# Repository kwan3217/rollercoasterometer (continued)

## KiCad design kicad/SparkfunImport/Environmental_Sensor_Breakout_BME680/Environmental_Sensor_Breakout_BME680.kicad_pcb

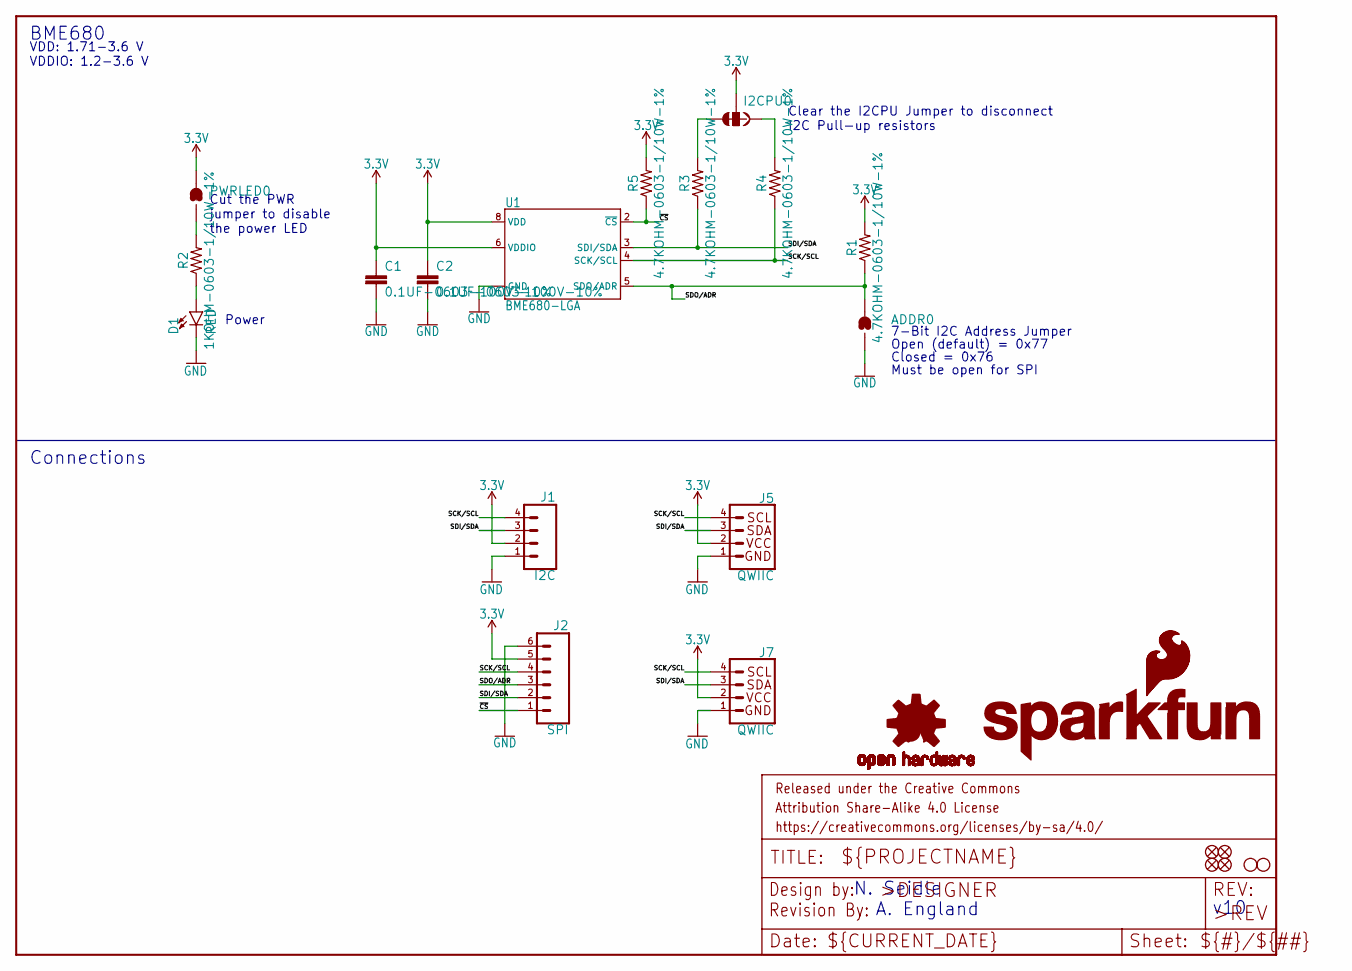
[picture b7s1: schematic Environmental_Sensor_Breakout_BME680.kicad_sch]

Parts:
ADDR0: JUMPER-SMT_2_NO_SILK; SMT-JUMPER_2_NO_SILK
C1, C2: 0.1UF-0603-100V-10%; C_0603_1608Metric
D1: RED; LED-0603
FD1, FD2, FD3, FD4: FIDUCIALUFIDUCIAL; FIDUCIAL-MICRO
FRAME1: FRAME-LETTER; CREATIVE_COMMONS
H1, H2: STAND-OFFTIGHT; STAND-OFF-TIGHT
I2CPU0: JUMPER-SMT_3_2-NC_TRACE_SILK; SMT-JUMPER_3_2-NC_TRACE_SILK
J1: I2C; 1X04_NO_SILK
J2: SPI; 1X06_NO_SILK
J5, J7: QWIIC; JST_SH_SM04B-SRSS-TB_1x04-1MP_P1.00mm_Horizontal
LOGO1: OSHW-LOGOMINI; OSHW-LOGO-MINI
LOGO2: SFE_LOGO_NAME_FLAME.1_INCH; SFE_LOGO_NAME_FLAME_.1
LOGO3: REVISION
LOGO4: SFE_LOGO_FLAME.1_INCH; SFE_LOGO_FLAME_.1
PWRLED0: JUMPER-SMT_2_NC_TRACE_SILK; SMT-JUMPER_2_NC_TRACE_SILK
R1, R3, R4, R5: 4.7KOHM-0603-1/10W-1%; R_0603_1608Metric
R2: 1KOHM-0603-1/10W-1%; R_0603_1608Metric
U1: BME680-LGA; Bosch_LGA-8_3x3mm_P0.8mm_ClockwisePinNumbering

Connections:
3.3V: C1.1, C2.1, I2CPU0.2, J1.2, J2.5, J5.2, J7.2, PWRLED0.2, R1.2, R5.2, U1.6 (VDDIO), U1.8 (VDD)
/SCK/SCL: J1.4, J2.4, J5.4, J7.4, R4.1, U1.4 (SCK/SCL)
/SDI/SDA: J1.3, J2.2, J5.3, J7.3, R3.1, U1.3 (SDI/SDA)
/SDO/ADR: ADDR0.2, J2.3, R1.1, U1.5 (SDO/ADR)
/~CS: J2.1, R5.1, U1.2 (~CS)
GND: ADDR0.1, C1.2, C2.2, D1.C, J1.1, J2.6, J5.1, J7.1, U1.1 (GND), U1.7 (GND)
unnamed: D1.A, R2.1
unnamed: I2CPU0.1, R4.2
unnamed: I2CPU0.3, R3.2
unnamed: PWRLED0.1, R2.2

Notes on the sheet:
7-Bit I2C Address Jumper
Connections
Clear the I2CPU Jumper to disconnect I2C Pull-up resistors
BME680
VDD: 1.71-3.6 V VDDIO: 1.2-3.6 V
Cut the PWR jumper to disable the power LED
Closed = 0x76
Power
N. Seidle
A. England
Open (default) = 0x77
Must be open for SPI
v10

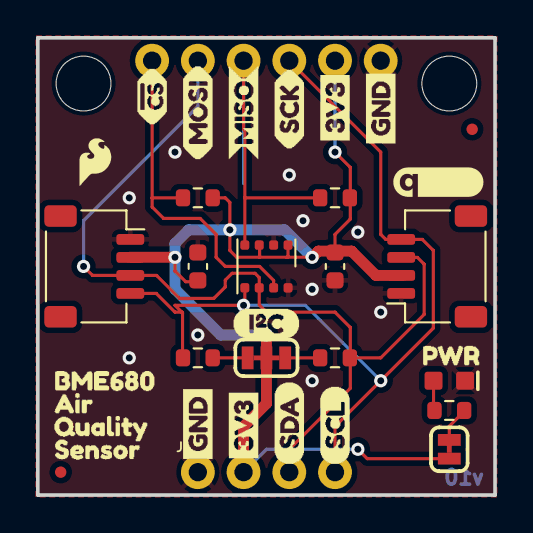
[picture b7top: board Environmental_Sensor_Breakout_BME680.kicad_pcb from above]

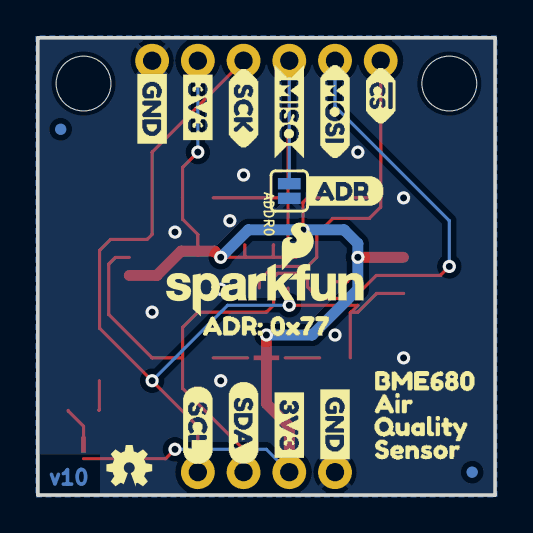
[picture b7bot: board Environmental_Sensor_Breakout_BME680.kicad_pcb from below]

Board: 2 copper layers, 25.4 x 25.4 mm, 60 parts (21 on the bottom side), 10 nets.

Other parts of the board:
U$1, U$2: MISO_O
U$3, U$4: !CS_I
U$5, U$6: MOSI_I
U$7, U$8: SCK_I
U$9, U$10, U$16, U$17: 3V3_P
U$11, U$12, U$13, U$14: GND_P
U$15: I2C
U$18, U$19: SDA_IO
U$20, U$21: SCL_IO
U$22, U$26: BME6800
U$23, U$27: AIR1
U$24, U$28: QUALITY2
U$25, U$29: SENSOR3
U$30: ADR4
U$32: QWIIC_5MM
U$33: ADR#_0X770
U$34: PWR_TO

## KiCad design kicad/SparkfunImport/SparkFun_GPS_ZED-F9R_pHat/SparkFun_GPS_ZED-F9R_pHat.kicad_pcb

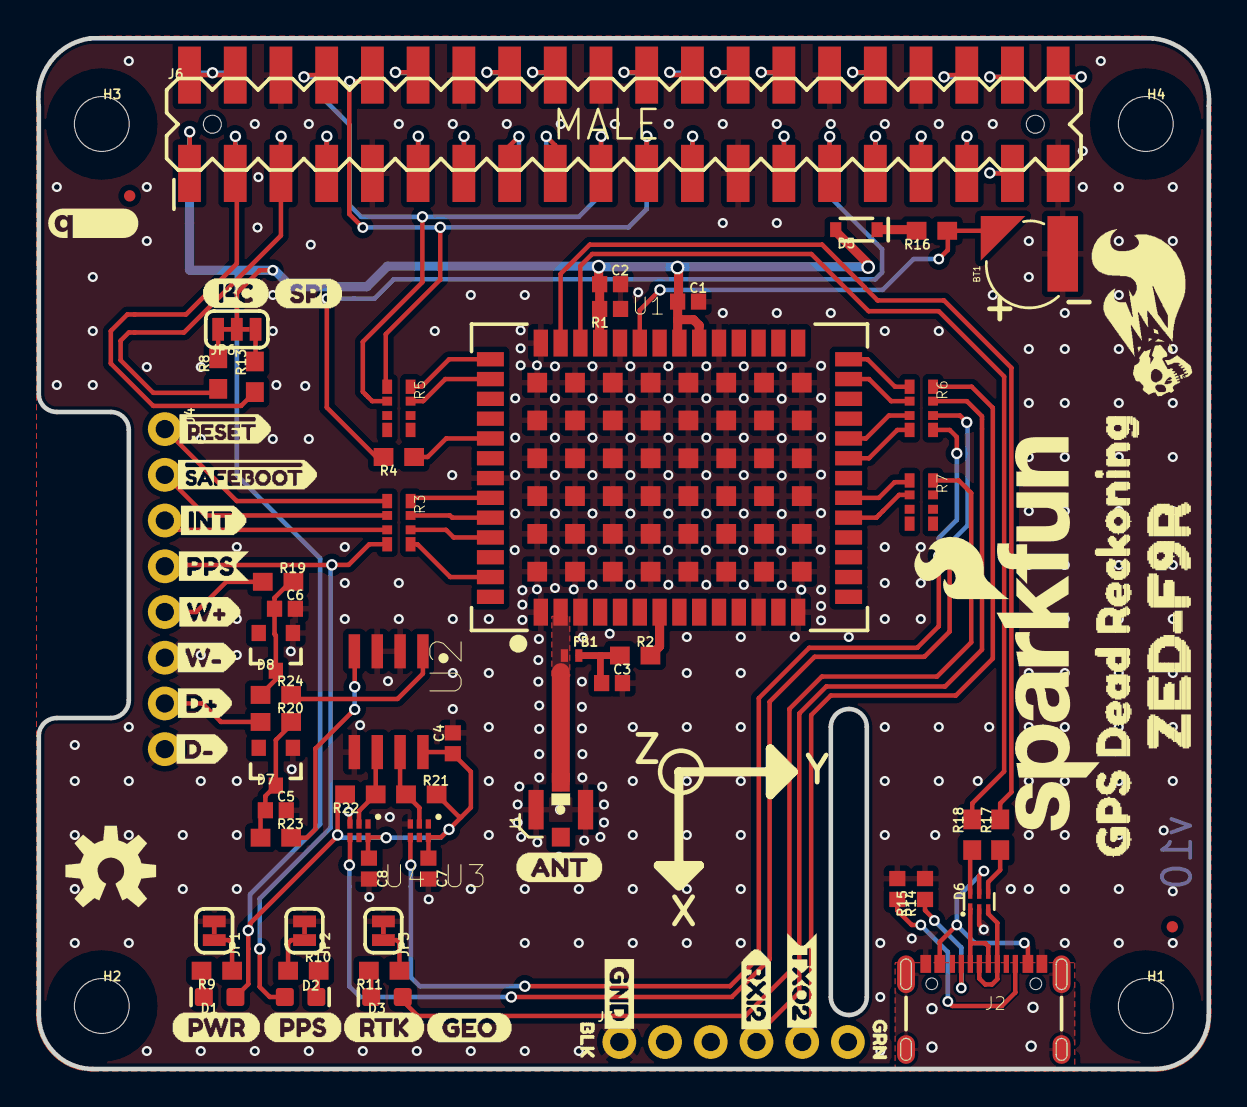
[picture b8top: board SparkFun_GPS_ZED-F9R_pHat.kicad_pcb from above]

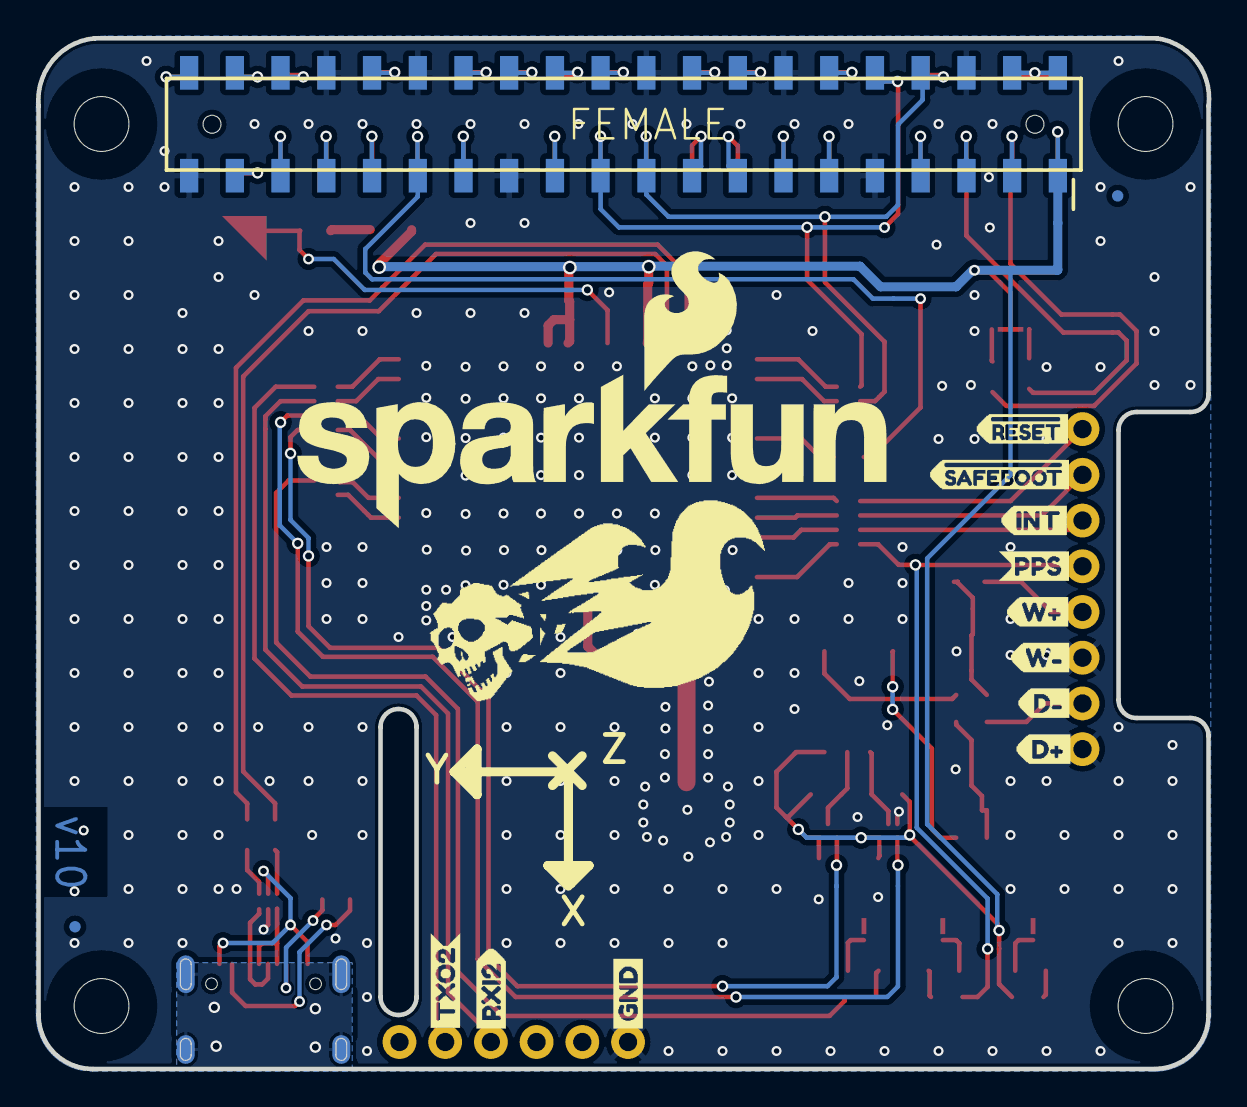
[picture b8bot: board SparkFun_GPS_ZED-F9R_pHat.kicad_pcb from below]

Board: 2 copper layers, 65.0 x 57.3 mm, 101 parts (15 on the bottom side), 84 nets.

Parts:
BT1: ML414H_IV01E_BATTERY; ML414H_IV01E
C1, C2: 1.0uF; 0402
C3: 47pF; 0402
C4, C7, C8: 0.1uF; 0402
C5, C6: 1nF; 0402
D1: RED; LED-0603
D2, D3: BLUE; LED-0603
D5: 0.5A/40V/420mV; SOD-323
D6: PRTR5V0U2F; SOT886
D7, D8: 15V; SOT23-3
FB1: 120NH; 0402_MURATA
FD1, FD2, FD3, FD4: FIDUCIALUFIDUCIAL; FIDUCIAL-MICRO
FRAME1: FRAME-LEDGER; CREATIVE_COMMONS
H1, H2, H3, H4: STAND-OFFTIGHT; STAND-OFF-TIGHT
J1: U.FL
J2: USB-C-16P
J3: 1X06_NO_SILK
J4: 1X08_NO_SILK
J6: RASPBERRYPI-40-PIN-GPIO_SMD_STACK_NOHOLES_NOREF; RASPBERRY_PI_HAT_40_PIN_SMD_STACKABLE_NOHOLES_NOREF
JP1, JP2, JP3: JUMPER-SMT_2_NC_TRACE_SILK; SMT-JUMPER_2_NC_TRACE_SILK
JP6: JUMPER-SMT_3_2-NC_TRACE_SILK; SMT-JUMPER_3_2-NC_TRACE_SILK
LOGO1: QWIIC_LOGO_5MM; QWIIC_5MM
LOGO2: OSHW-LOGOM; OSHW-LOGO-M
LOGO3: SFE_LOGO_NAME_FLAME.2_INCH; SFE_LOGO_NAME_FLAME_.2
R1: 100K; 0402
R2, R4: 33; 0603
R3, R5, R6, R7: 33; 1206_RA
R8, R13: 2.2k; 0603
R9, R10, R11: 1k; 0603
R14, R15: 5.1k; 0402
R16, R19, R20: 3.3k; 0603
R17, R18: 27; 0603
R21, R22: 910; 0603
R23, R24: 470; 0603
U1: U-BLOX_ZED_F9R; UBLOX_ZED_F9R
U2: DUAL-OPTO_HCPL-073L; SOP_8-PIN
U3, U4: UHS_INVERTER_SCHMITT_TRIGGERSIP6; SIP6
U$1: INT1
U$2: PPS4
U$3: PPS6
U$4: PWR7
U$5: RTK5
U$6: RXI28
U$7: #RESET1
U$8: #RESET2
U$9: SFE_LOGO_NAME_FLAME_.3
U$10: TXO21
U$11: INT2
U$12: PPS1
U$13: #SAFEBOOT0
U$14: RXI26
U$15: #SAFEBOOT3
U$16: TXO25
U$17: BLK2
U$18, U$19: GND-04
U$20: I_SUPER2_C-()-04
U$21: ANT1
U$22, U$32: D#0
U$23, U$33: D#1
U$24: SPI0
U$25: GPS_DEAD_RECKONING0
U$26: ZED#F9R0
U$27, U$34: W#2
U$28, U$35: W#3
U$29: GEO0
U$30: GRN1
U$31, U$36: DEAD#RECKONING#GPS#BOARD#SILK#FINAL#JPG

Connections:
3.3V: C1.1, C2.1, C4.1, C7.1, C8.1, D1.A, D5.A, J6.1, J6.1B, J6.17, J6.17B, JP6.2, R1.2, R21.2, R22.2, U1.P33, U1.P34, U1.P38, U2.P8, U3.P6, U4.P6
5V: J6.2, J6.2B, J6.4, J6.4B
CE1: J6.26, J6.26B
DIR+: J4.7, R20.1
DIR_IN: R23.2, U2.P4
DIR_OUT: R6.P6, U4.P4
DIR_SCHMITT: R22.1, U2.P6, U4.P2
DMINUS: R18.2, U1.P39
DPLUS: R17.2, U1.P40
GND: BT1.-, C1.2, C2.2, C3.2, C4.2, C5.2, C6.2, C7.2, C8.2, D6.2, D7.1, D8.1, J1.1, J1.2, J2.GND, J2.GND2, J3.1, J4.6, J4.8, J6.6, J6.6B, J6.9, J6.9B, J6.14, J6.14B, J6.20, J6.20B, J6.25, J6.25B, J6.30, J6.30B, J6.34, J6.34B, J6.39, J6.39B, JP1.1, JP2.1, JP3.1, R1.1, R14.1, R15.1, U1.G1, U1.G2, U1.G3, U1.G4, U1.G5, U1.G6, U1.G7, U1.G8, U1.G9, U1.G10, U1.G11, U1.G12, U1.G13, U1.G14, U1.G15, U1.G16, U1.G17, U1.G18, U1.G19, U1.G20, U1.G21, U1.G22, U1.G23, U1.G24, U1.G25, U1.G26, U1.G27, U1.G28, U1.G29, U1.G30, U1.G31, U1.G32, U1.G33, U1.G34, U1.G35, U1.G36, U1.G37, U1.G38, U1.G39, U1.G40, U1.G41, U1.G42, U1.G43, U1.G44, U1.G45, U1.G46, U1.G47, U1.G48, U1.P1, U1.P3, U1.P12, U1.P14, U1.P32, U1.P37, U1.P41, U1.P48, U2.P2, U2.P3, U2.P5, U3.P3, U4.P3
GP4: J6.7, J6.7B
GP6: J6.31, J6.31B
GP12: J6.32, J6.32B
GP13: J6.33, J6.33B
GP16: J6.36, J6.36B
GP17: J6.11, J6.11B
GP18: J6.12, J6.12B
GP19: J6.35, J6.35B
GP20: J6.38, J6.38B
GP21: J6.40, J6.40B
GP22: J6.15, J6.15B
GP23: J6.16, J6.16B
GP24: J6.18, J6.18B
GP25: J6.22, J6.22B
GP26: J6.37, J6.37B
GP27: J6.13, J6.13B
ID_SC: J6.28, J6.28B
ID_SD: J6.27, J6.27B
INT: J4.3, R3.P3
unnamed: JP6.1, R13.2
unnamed: D5.C, R16.2
unnamed: JP6.3, R8.2
unnamed: D1.C, R9.2
unnamed: C3.1, FB1.P2, R2.1
unnamed: D6.6, R18.1
unnamed: D6.4, R17.1
unnamed: JP1.2, R9.1
unnamed: D6.3, J2.A6, J2.B6
unnamed: D6.5, J2.VBUS1, J2.VBUS2
unnamed: D6.1, J2.A7, J2.B7
unnamed: J2.B5, R14.2
unnamed: R3.P8, U1.P49
unnamed: R3.P6, U1.P51
unnamed: R5.P6, U1.P44
unnamed: J2.A5, R15.2
unnamed: R5.P5, U1.P45
unnamed: R4.1, U1.P46
unnamed: R5.P8, U1.P42
unnamed: JP3.2, R11.1
unnamed: JP2.2, R10.1
unnamed: D2.C, R10.2
unnamed: D3.C, R11.2
unnamed: R5.P7, U1.P43
unnamed: C6.1, D8.3, R19.2, R24.1
unnamed: R7.P2, U1.P19
unnamed: R7.P1, U1.P20
unnamed: R3.P5, U1.P53
unnamed: R3.P7, U1.P50
unnamed: R6.P1, U1.P27
unnamed: R6.P2, U1.P26
unnamed: R6.P4, U1.P22
unnamed: R6.P3, U1.P23
unnamed: C5.1, D7.3, R20.2, R23.1
PPS: D2.A, J4.4, R3.P4
QWIIC_SCL: J6.5, J6.5B, R8.1
QWIIC_SDA: J6.3, J6.3B, R13.1
RF_IN: FB1.P1, J1.FEED, U1.P2
RTK_STAT: D3.A, R7.P8
RXI2: J3.4, R6.P7
RXI/MOSI: J6.8, J6.8B, J6.19, J6.19B, R5.P2
SCL/CLK: J6.23, J6.23B, R5.P4
SDA/~CS: J6.24, J6.24B, R5.P3
SHIELD: J2.SHLD1, J2.SHLD2, J2.SHLD3, J2.SHLD4, J2.SHLD5, J2.SHLD6, J2.SHLD7, J2.SHLD8
TXO2: J3.5, R6.P8
TXO/MISO: J6.10, J6.10B, J6.21, J6.21B, R5.P1
TX_READY: J6.29, J6.29B, R4.2
V_BATT: BT1.+, R16.1, U1.P36
V_RF: R2.2, U1.P7
WT+: J4.5, R19.1
WT_IN: R24.2, U2.P1
WT_OUT: R6.P5, U3.P4
WT_SCHMITT: R21.1, U2.P7, U3.P2
~RESET: J4.1, R3.P1
~SAFEBOOT: J4.2, R3.P2

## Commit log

2022-04-15 Added schematic blocks
2022-04-15 Moved stuff into a kicad folder
2022-04-15 More project checkin and reorganization
2022-04-15 Added read_sensors Arduino sketch and ICM42688 breakout
2022-04-15 Adding teensy_loader_cli as a submodule
2022-04-15 Added readme
2022-04-15 Broke down sensor block into a tree of sheets
2022-04-15 Updating README to include efforts to bring up CLI
2022-04-15 Giving up on CLI for now
2022-04-15 Adding rollercoasterometer.ino . It's not much now, but it will grow into the foundation of the program that will run on the final rollercoasterometer.
2022-04-15 Moved the Arduino sketch to its own folder, to satisfy the IDE
2022-04-18 One shining moment -- I2C_sensor lower-level stuff is working. Moving to different computer.
2022-04-18 Added Makefile and linker script for if/when we ever get back to command-line compiling
2022-04-18 Added USB+ breakout.
2022-04-18 Added a readme for the USB+ breakout
2022-04-18 Added kwan_kicad_lib as a submodule
2022-04-18 Updated README.md
    This readme is pretty much a journal of my development of the firmware for the Teensy 4.1 that will be riding on the rollercoasterometer.
2022-04-19 Moved submodule to within kicad folder
2022-04-19 Updated submodules
2022-04-19 Use updated kwan_kicad_lib
2022-04-19 Added Digikey references
2022-04-19 One shining moment
    Commit board while it still works
2022-04-20 Added AVR sketches for reading out sensors
2022-04-20 Updated symbol
    This incorporates the change in the library, to offset the NC pins and satisfy the ERC
2022-04-20 Added Digikey numbers and purposes to several parts
2022-04-20 Changed value of R436
    This is the current limiter for the battery charging. It slows down the charging, in exchange for reducing the number of different components
2022-04-20 Updated Digikey part numbers
    Darn supply chain crisis :(
2022-04-20 Updated values for I2C pullup resistors
    This weakens the pullup a little bit in exchange for a reduced part count
2022-04-20 Updated part numbers
    This sheet is included multiple times, and this time it decided to save with the references from a different instance.
2022-04-20 Added project tables
    It looks like these are appropriate to commit
2022-04-20 Updated submodule
2022-04-20 Updated part number
    Darn supply chain crisis :(
2022-04-20 Updated .gitignore to ignore bills of materials and project archives
2022-04-20 Updating PCB to follow schematic
2022-04-20 Updated graphical symbols
2022-04-20 Updated Digikey part numbers
2022-04-20 Changed resistor values to reduce component type count
2022-04-20 Changed regulator manufacturer
    New parts with identical pinout
2022-04-20 Updated graphical elements
2022-04-20 Changed protection diode for USB lines
2022-04-20 Updated Digikey part number
2022-04-20 Edited symbol to remove ERC violations
    Some of the overlapping NC pins were getting connected through the NC symbol (not connected to anything else, but connected to each other). This is fixed by editing this instance of the symbol and of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
2022-04-20 Renamed image
2022-04-20 Updated PCB
    Updated ESD diode and routing of lines through it. Added corner silkscreen marks around all LGA/BGA parts, to allow easier inspection of placement before reflow.
2022-04-20 Updated which lines are used in 4-line protection diode
2022-04-24 Added a purpose field to bypass capacitors
2022-04-24 Updated purposes for regulators
2022-04-25 Updated antenna chain
    Added a BOM-only part to give the actual antenna a Digikey reference that won't appear on the PCB. Added a solder jumper to control whether the antenna is powered. Removed 27R resistors for pins that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
2022-04-25 Updated Digikey numbers
2022-04-25 Corrected Digikey numbers
    Stupid supply chain :( . Updated protection diode for data lines. Removed heirarchical pins which are no longer present in the nested sheet.
2022-04-25 Updated kwan_kicad_lib
2022-04-25 Added joystick board
2022-04-25 Updated PCB to follow schematic changes
2022-04-25 Added reference to USB cable on BOM
2022-04-25 Updated LEDs and edge cutouts
2022-04-25 Added reference to TeensyView
    TeensyView does not get a footprint because it mounts on top of the Teensy, but it is hooked up to the schematic properly.
2022-04-25 Updated project file
2022-04-25 Replaced JS5208 with smaller JS1400
2022-04-25 Added joystick as a STEP part and used it as part of Teensy 3D model
    The whole board was saved as joystick.kicad_pcb. The parts of the board that are not part of the joystick board were removed. The board was then washed through the Freecad plugin KicadStepUp to conve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
2022-04-28 Added graphical components to schematic for joystick board
2022-04-28 Numbering change
2022-04-28 Added pocket case design files
2022-04-28 Added freecad stuff to gitignore
2022-04-28 Moved USB+ connectors to bottom of board
2022-04-28 Added #include guard
2022-04-28 Added code for ICM2 and ICM4 at the same time
2022-04-28 Added code for icm42688
2022-04-28 Added lib table stuff
2022-04-28 Updated gitignore
2022-04-29 Added a NC to the board
2022-04-29 Added code to handle SD card and write ublox packets
2022-05-14 Import from arduino-1.8.19/hardware/teensy/avr/cores/teensy4
2022-12-18 Checkin before branch
2022-12-18 Added rollercoasterometer_hat before branch
2022-12-18 Track current version of submodule
2023-03-10 Commit as-ordered shipometer 23.03
2023-03-14 Updated to KiCad 7.0
2023-03-18 Improved grounding and bypass caps on GPS
2023-03-19 Added imported Sparkfun projects. Some of them have had their footprints changed so that the 3d models work.
2023-03-19 Starting to make gps_breakout
2023-03-19 Added .gitingonre
2023-03-21 Added BME280 and ICM20948 stamps
2023-03-21 Updated several parts to kicad7, added models
2023-03-21 Added compressed wrl file
2023-03-21 Renamed
2023-03-21 Rotate IMU stamp to match GPS
2023-03-22 Update __init__.py
    check in new version of scaling script
2023-03-22 Finished and decorated IMU stamp
2023-03-24 Added labels to BME280 stamp
2023-03-24 Added labels to white LEDs
2023-03-24 Copied from rollercoasterometer_hat_sf
2023-03-24 Added initial version of readme
2023-03-25 Imported the two stamp designs
2023-03-25 Changed pointers from rollercoasterometer_hat_sf to shipometer
2023-03-25 Imported BME280 stamp
2023-03-25 Pulled in ICM20948
2023-03-25 Update kwan_kicad_lib
2023-04-03 Added missing files
2023-04-03 As ordered on 03 Apr 2023. Some but not all numbers-on-hand have been updated.
2023-04-05 Updated numbers on hand and numbers in cart
2023-04-09 Added mechanical drawings for case
2023-04-09 Moved Ponoko design to a subfolder under Mechanical
2023-04-09 Updated number on hand, and added more Digikey/Mouser/Mfg numbers
2023-10-16 Update .gitignore files
2023-10-16 Updated stuff that was needed to make Shipometer 23.04 case
